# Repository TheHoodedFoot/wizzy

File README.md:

<div align="center">

</div>

# Wizzy

Wizzy is a WYSIWYG camera driver system for use with laser engraving machines.

## Description

- Write a short introduction to the project.
- If you are using badges, add them here.

# :ledger: Index

- [About](#beginner-about)
- [Usage](#sunny-usage)
  - [Installation](#electric_plug-installation)
  - [Commands](#package-commands)
- [Development](#wrench-development)
  - [Pre-Requisites](#notebook-pre-requisites)
  - [Developmen Environment](#nut_and_bolt-development-environment)
  - [File Structure](#file_folder-file-structure)
  - [Build](#hammer-build)  
  - [Deployment](#rocket-deployment)  
- [Community](#cherry_blossom-community)
  - [Contribution](#fire-contribution)
  - [Branches](#cactus-branches)
  - [Guideline](#exclamation-guideline)  
- [FAQ](#question-faq)
- [Resources](#page_facing_up-resources)
- [Gallery](#camera-gallery)
- [Credit/Acknowledgment](#star2-creditacknowledgment)
- [License](#lock-license)

# :beginner: Getting Started
Add a detailed introduction about the project here, everything you want the reader to know.

# :sunny: Usage
Write about how to use this project.

###  :electric_plug: Installation
- Steps on how to install this project, to use it.
- Be very detailed here, For example, if you have tools which run on different operating systems, write installation steps for all of them.

```
$ add installations steps if you have to.
```

###  :package: Commands
- Commands to start the project.

#  :wrench: Development
If you want other people to contribute to this project, this is the section, make sure you always add this.

### :notebook: Pre-Requisites
List all the pre-requisites the system needs to develop this project.
- A tool
- B tool

###  :nut_and_bolt: Development Environment
Write about setting up the working environment for your project.
- How to download the project...
- How to install dependencies...

###  :file_folder: File Structure
Add a file structure here with the basic details about files, below is an example.

```
.
├── assets
│   ├── css
│   │   ├── index-ui.css
│   │   └── rate-ui.css
│   ├── images
│   │   ├── icons
│   │   │   ├── shrink-button.png
│   │   │   └── umbrella.png
│   │   ├── logo_144.png
│   │   └── Untitled-1.psd
│   └── javascript
│       ├── index.js
│       └── rate.js
├── CNAME
├── index.html
├── rate.html
└── README.md
```

| No | File Name | Details 
|----|------------|-------|
| 1  | index | Entry point

###  :hammer: Build
Write the build Instruction here.

### :rocket: Deployment
Write the deployment instruction here.

# :cherry_blossom: Community

If it's open-source, talk about the community here, ask social media links and other links.

 ###  :fire: Contribution

 Your contributions are always welcome and appreciated. Following are the things you can do to contribute to this project.

 1. **Report a bug** <br>
 If you think you have encountered a bug, and I should know about it, feel free to report it [here]() and I will take care of it.

 2. **Request a feature** <br>
 You can also request for a feature [here](), and if it will viable, it will be picked for development.  

 3. **Create a pull request** <br>
 It can't get better then this, your pull request will be appreciated by the community. You can get started by picking up any open issues from [here]() and make a pull request.

 > If you are new to open-source, make sure to check read more about it [here](https://www.digitalocean.com/community/tutorial_series/an-introduction-to-open-source) and learn more about creating a pull request [here](https://www.digitalocean.com/community/tutorials/how-to-create-a-pull-request-on-github).

 ### :cactus: Branches

 I use an agile continuous integration methodology, so the version is frequently updated and development is really fast.

1. **`Master`** is the development branch.

2. **`Production`** is the production branch.

3. No further branches should be created in the main repository.

**Steps to create a pull request**

1. Make a PR to `master` branch.
2. Comply with the best practices and guidelines e.g. where the PR concerns visual elements it should have an image showing the effect.
3. It must pass all continuous integration checks and get positive reviews.

After this, changes will be merged.

### :exclamation: Guideline
codding guidelines or other things you want people to follow should follow.

# :question: FAQ
You can optionally add a FAQ section about the project.

#  :page_facing_up: Resources
Add important resources here

#  :camera: Gallery
Pictures of your project.

# :star2: Credit/Acknowledgment
Credit the authors here.

#  :lock: License
Add a license here, or a link to it.

---

# :bar_chart: Charts and Diagrams

## :mermaid: Mermaid
```mermaid
pie
"Movies" : 80
"TV shows" : 20
```

## :1234: TeX Mathematics
$$
x = {-b \pm \sqrt{b^2-4ac} \over 2a}
$$

## :warning: Alerts

> [!NOTE]
> Useful information that users should know, even when skimming content.

> [!TIP]
> Helpful advice for doing things better or more easily.

> [!IMPORTANT]
> Key information users need to know to achieve their goal.

> [!WARNING]
> Urgent info that needs immediate user attention to avoid problems.

> [!CAUTION]
> Advises about risks or negative outcomes of certain actions.

More information on markdown can be found on [Github](https://docs.github.com/en/get-started/writing-on-github/getting-started-with-writing-and-formatting-on-github/basic-writing-and-formatting-syntax)

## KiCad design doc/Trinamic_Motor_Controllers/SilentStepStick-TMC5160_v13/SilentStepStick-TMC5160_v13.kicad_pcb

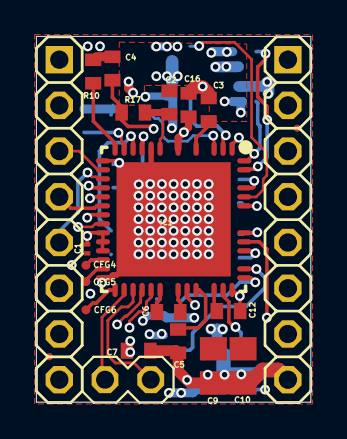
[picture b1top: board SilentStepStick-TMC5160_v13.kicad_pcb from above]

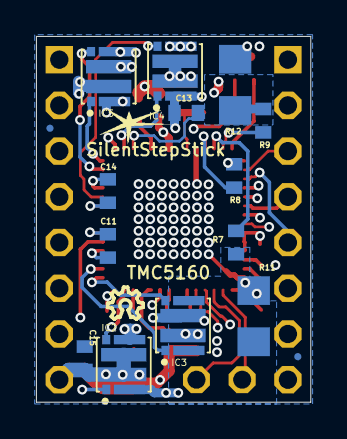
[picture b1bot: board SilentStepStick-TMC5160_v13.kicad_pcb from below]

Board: 6 copper layers, 15.2 x 20.3 mm, 39 parts (17 on the bottom side), 44 nets.

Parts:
C1: 100nF; C0201
C2, C3: 2u2; C0402
C4: 470nF; C0402
C5, C7, C11, C12, C13, C14: 100nF; C0402
C6: 22nF; C0402
C9, C10: 10uF/35V; C0805
C15, C16: 470nF/35V; C0402
CFG4, CFG5, CFG6: PAD-0.5_NC
IC1: TMC5160-WA; VQFN56(47)_8.0X8.0X0.9MM_0.5P_EP
IC2, IC3, IC4, IC5: FDMC8030; 8-POWERWDFN
LOGO1: LOGO_SPARK-2; SPARK_2MM
LOGO2: LOGO_OSHW-2; OSHW_2MM
P1, P2: MA08-1; 1X08-S
P3: MA02-1
R7, R8, R9, R10: 47R; R0402
R11, R12: 75mR; R1206
R17: 2R2/1%; R0402
X1, X2, X3, X4: PASSER-04; PASSER_04MM

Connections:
5V_OUT: C2.2, IC1.6, R17.2
+VM: C5.2, C7.2, C9.1, C10.1, C15.2, C16.2, IC1.5, IC1.33, IC2.P$D1, IC2.P$D2, IC4.P$D1, IC4.P$D2, P2.8
BMA1: C11.1, IC1.40, IC2.P$4, IC3.P$D1, P2.5
BMA2: C12.2, IC1.37, IC2.P$5, IC3.P$D2, P2.6
BMB1: C13.1, IC1.1, IC4.P$4, IC5.P$D1, P2.4
BMB2: C14.2, IC1.45, IC4.P$5, IC5.P$D2, P2.3
CA1: C11.2, IC1.42
CA2: C12.1, IC1.35
CB1: C13.2, IC1.3
CB2: C14.1, IC1.43
CLK: IC1.13, P1.3
CSN: IC1.14, P1.5
DIAG0: IC1.27, P3.2
DIAG1: IC1.28, P3.1
DIR: IC1.19, P1.1
EN: IC1.29, P1.8
GND: C1.1, C2.1, C3.1, C4.1, C7.1, C9.2, C10.2, C15.1, C16.1, IC1.7, IC1.12, IC1.25, IC1.48, P2.1, P2.7, R8.2, R10.2, R11.1, R12.1
HA1: IC1.41, IC2.P$1
HA2: IC1.36, IC2.P$8
HB1: IC1.2, IC4.P$1
HB2: IC1.44, IC4.P$8
LA1: IC1.39, IC3.P$1
LA2: IC1.38, IC3.P$8
LB1: IC1.47, IC5.P$1
LB2: IC1.46, IC5.P$8
unnamed: C6.2, IC1.32
unnamed: C6.1, IC1.31
unnamed: C3.2, IC1.4
unnamed: C5.1, IC1.34
unnamed: CFG6.1, IC1.26
unnamed: CFG4.1, IC1.23
unnamed: CFG5.1, IC1.24
SA: IC3.P$4, IC3.P$5, R7.2, R11.2
SB: IC5.P$4, IC5.P$5, R9.2, R12.2
SCK: IC1.15, P1.6
SDI: IC1.16, P1.7
SDO: IC1.17, P1.4
SRAH: IC1.9, R7.1
SRAL: IC1.8, R8.1
SRBH: IC1.10, R9.1
SRBL: IC1.11, R10.1
STEP: IC1.18, P1.2
VCC: C4.2, IC1.30, R17.1
VCC_IO: C1.2, IC1.20, IC1.21, IC1.22, P2.2

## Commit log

2024-04-02 Initial commit; LFS test
2024-04-02 Add initial models for bracket and test stand
2024-09-08 Add bracket assembly; Gitea actions
    Adds the first version of the bracket assembly in FreeCAD format.
    Also adds some documentation and boilerplate PlatformIO code.
    Includes a Gitea action to run make and build the code.
2024-09-08 Update README to show correct badge
    The default runner is arm64, so set the badge to display that instead of
    amd64.
2024-09-14 Add Owlsight capture script
    Adds a simple script that uses ssh to login to the camera, capture a
    photo, and transfer it to the /tmp directory
2024-09-16 Add example mjpeg server code
2024-09-16 Improve capture settings
2024-09-16 Change Python autofocus code
    Changes the code according to the Arducam documentation. Hopefully this
    should enable continuous autofocus.
2024-09-19 Add calibration PDF
2024-09-23 Fix Apriltags generator script
    The script that is provided with Apriltags for the purpose of converting
    png images to SVG does not work correctly, so it is modified here.
2024-10-06 Add apriltags submodule
2024-10-08 Add Apriltags images; Fix tag script
    The script supplied by Apriltags for converting png files to svg does
    not work correctly. This applies a fix.
2024-10-08 Remove apriltag-imgs and add apriltag-generation
2024-10-13 Add PDF from calibration branch
2024-10-27 Copy example apriltags code
    Creates a template for further work on still images.
2024-10-27 Add missing files from previous commit
2024-11-17 Add OpenCV calibration example
2024-11-17 Hardcode libraries instead of pkg-config
    Ubuntu's opencv does not have the files for pkg-config, so we hardcode
    the libraries.
2024-11-17 Fixes to compile on Ubunto
    Stripped out the Aruco tags code, which is missing on Ubuntu
2024-11-24 Add streaming notes and virtual camera submodule
2024-11-26 Add modified OpenCV calibration example
2024-11-28 Remove unused Makefile target
2024-12-01 Update slide assembly for Freecad 1.0 assembly workbench
2024-12-03 feat: Add hello.c and update Makefile for building and running C program
2024-12-08 Update platformio.ini to ignore raspicam
2024-12-08 Add basic videocapture OpenCV example
2024-12-08 Add aider branch
2024-12-09 Add working simple libcamera example
2024-12-09 Add simple-cam to platformio.ini ignore
2024-12-10 Remove duplicated simple-cam code
2024-12-13 Improve Makefile and generate compilation database
2024-12-13 Add LCCV submodule
2024-12-21 Update git lfs hooks
2024-12-22 Add openMVG submodule
2024-12-24 Update main Makefile to build simplecam
2024-12-26 Enable capture using Raw; Rename to wizzcam
